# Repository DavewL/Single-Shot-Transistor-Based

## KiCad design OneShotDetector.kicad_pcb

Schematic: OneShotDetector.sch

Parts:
C1, C2: 1uf; C_1206_HandSoldering
C3, C4: 1000pf; C_1206_HandSoldering; Voltage 100V
D1, D2, D3, D4: D_Schottky
D5, D6: D_Zener_Small; D_SOD-323_HandSoldering; PartNumber YFZVFHTR5.1B
HDR1: AB2_HDR03-1; 39-30-1039
HDR2, HDR3: AB2_HDR02-1; 39-29-9023
POT1: TC33X-2-103E; Trimpot_3.8mmx3.6mm_TC33X-2-103E; MPN TC33X-2-103E; Digi-Key_PN TC33X-103ETR-ND
Q1: SQ2361ES; SOT-23
R1: 30k; R_0805_HandSoldering
R2, R4: 1000k; R_0805_HandSoldering
R3: 10k; R_0805_HandSoldering
R5: 300k; R_0805_HandSoldering
U1: TLV6703DDCT; SOT-23-6_Handsoldering
U2: ZXMS6004DN8; SO-8_5.3x6.2mm_Pitch1.27mm
U3: NCP781BMN150TAG; DFN-6-1EP_3x3mm_Pitch0.65mm

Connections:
+15V: C1.1, C3.2, Q1.2, R1.2, R2.1, R4.1, U1.5 (VDD), U3.5 (OUT), U3.6 (ADJ/SEN)
GNDREF: C1.2, C2.1, C4.1, D5.2 (A), D6.2 (A), HDR1.2, HDR2.2, HDR3.2, POT1.3 (CW), R4.2, R5.2, U1.2 (GND), U1.4 (GND), U1.6 (GND), U2.1 (S2), U3.4 (GND), U3.EP
unnamed: C2.2, D6.1 (K), POT1.2 (Wiper), R2.2, U1.3 (SENS), U2.7 (D2), U2.8 (D2)
unnamed: C3.1, R3.2, R5.1
unnamed: C4.2, D3.1, D4.1, U3.1 (IN), U3.2 (EN)
unnamed: D1.1, D2.1, HDR1.1
unnamed: D1.2, Q1.3
unnamed: D2.2, HDR1.3
unnamed: D3.2, HDR2.1
unnamed: D4.2, HDR3.1
unnamed: D5.1 (K), R3.1, U2.2 (IN2)
unnamed: Q1.1, R1.1, U1.1 (OUT)

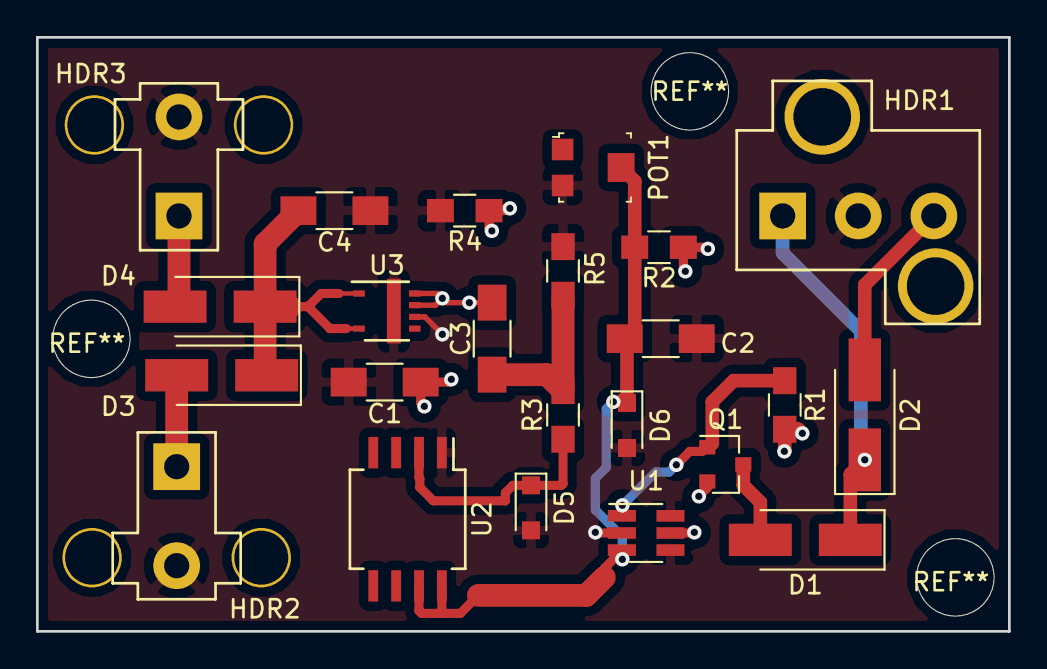
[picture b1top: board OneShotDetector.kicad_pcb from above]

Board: 2 copper layers, 54.0 x 33.0 mm, 23 parts (0 on the bottom side), 12 nets.

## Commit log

2018-08-20 updated to new KiCad version
